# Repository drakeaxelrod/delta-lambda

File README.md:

# Delta Lambda

ZMK firmware for the Delta Lambda 34-key split keyboard, running on two Seeed XIAO nRF52840 controllers. Based on the [delta-omega](https://github.com/unspecworks/delta-omega) design.

## Layout

**Gallium** alpha layout with home row mods (GACS order), 34 combos, mouse keys, and 6 layers.

### Base (Gallium)

- **Home row mods** (GACS): Gui/Alt/Ctrl/Shift on left, mirrored on right
- **Hyper** (all 4 mods) on W and F
- **Thumb layer-taps**: ESC/Util, Space/Nav, Enter/Num, Bksp/Fun

### Nav (hold Space)

### Num (hold Enter)

### Fun (hold Backspace)

### Util + Mouse (hold Escape)

### Game (toggle from Fun layer)

## Combos

| Type | Timeout | Prior idle | Examples |
|------|---------|------------|----------|
| Vertical (top+home) | 80ms | 150ms | `@` `#` `$` `%` `^` `+` `*` `&` |
| Vertical (home+bottom) | 80ms | 150ms | `` ` `` `\` `=` `~` `_` `-` `/` `\|` |
| Horizontal (adjacent) | 40ms | 280ms | `[` `]` `<` `(` `)` `>` `{` `}` |
| Multi-key | 50ms | 200ms | Tab (3-key), CapsWord, Studio unlock |
| Thumb | — | — | LShift, RShift |

## Home Row Mods

| Setting | Value |
|---|---|
| Flavor | balanced (positional hold-tap) |
| Tapping term | 280ms |
| Quick tap | 175ms |
| Require prior idle | 150ms |
| Hold trigger | opposite hand + thumbs only |

Thumb layer-taps use **balanced** flavor with 200ms tapping term for fast layer activation.

## Hardware

| Component | Detail |
|---|---|
| Base design | [delta-omega](https://github.com/unspecworks/delta-omega) |
| Controllers | 2x Seeed XIAO nRF52840 |
| Keys | 34 (3x5 + 2 thumb per hand) |
| Switches | Kailh Choc v1 / v2 (Hotswap) |
| Matrix | 4x10 (col2row) |
| Connection | USB-C or Bluetooth (5 profiles) |

## Building

### Local (Nix)

```bash
nix develop          # enter dev shell
just init            # initialize west workspace (first time)
just build           # build left + right + settings_reset
just bootloader      # download XIAO bootloader
just update          # west update
```

Outputs go to `build/`:
- `delta-lambda-left.uf2` (central)
- `delta-lambda-right.uf2` (peripheral)
- `delta-lambda-reset.uf2` (bond/settings reset)

### GitHub Actions

Push to `config/` or `boards/` triggers a build via ZMK's reusable workflow. Download UF2 artifacts from the Actions tab.

### Regenerate layer SVGs

```bash
just gen-svg    # regenerates assets/svg/layers/*.svg from keymap
```

## Flashing

1. Double-tap reset on the XIAO to enter UF2 bootloader (mounts as `XIAO-SENSE`)
2. Copy the appropriate `.uf2` file to the mounted drive
3. Flash left half first, then right half

To clear Bluetooth bonds, flash `delta-lambda-reset.uf2` on **both** halves, then reflash the regular firmware.

## ZMK Studio

Runtime keymap editing is enabled. Unlock with the combo at thumb key positions 30 + 33.

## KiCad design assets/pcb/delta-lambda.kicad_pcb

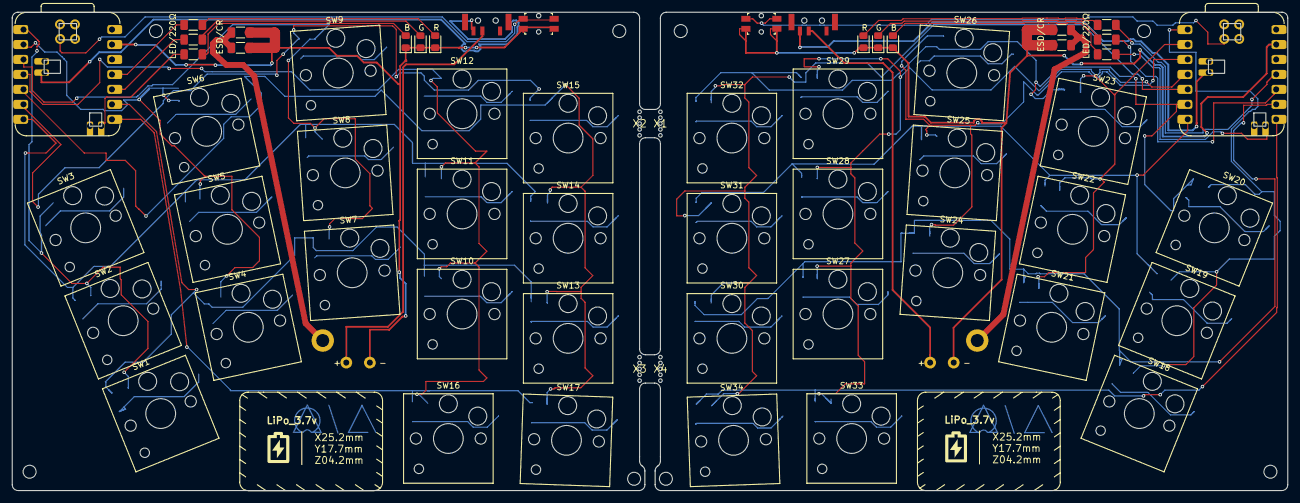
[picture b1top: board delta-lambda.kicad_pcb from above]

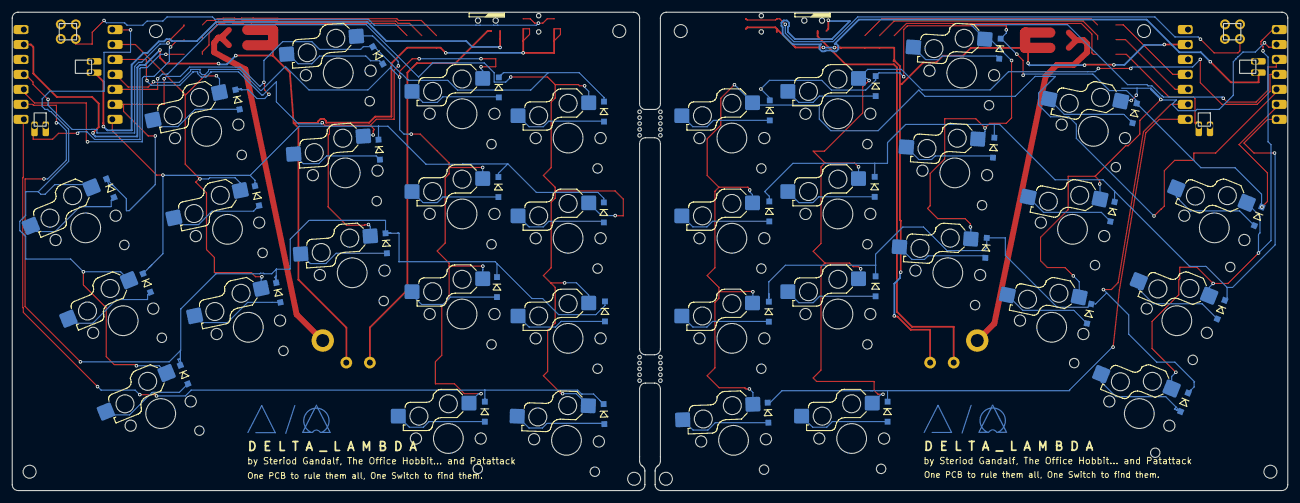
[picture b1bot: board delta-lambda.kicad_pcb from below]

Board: 2 copper layers, 216.5 x 81.2 mm, 106 parts (34 on the bottom side), 74 nets.

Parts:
C1, C2: C_1206_1NF; C_1206_3216Metric_Pad1.33x1.80mm_HandSolder
D1, D2, D3, D4, D5, D6, D7, D8, D9, D10, D11, D12, D13, D14, D15, D16, D17, D18, D19, D20, D21, D22, D23, D24, D25, D26, D27, D28, D29, D30, D31, D32, D33, D34: SOD123
H1, H2: mounting_hole_plated
L1, L4: LED_0805_R; LED_0805_2012Metric_Pad1.15x1.40mm_HandSolder
L2, L5: LED_0805_G; LED_0805_2012Metric_Pad1.15x1.40mm_HandSolder
L3, L6: LED_0805_B; LED_0805_2012Metric_Pad1.15x1.40mm_HandSolder
MCU1, MCU2: XIAO-nRF52840-SMD; smdXIAO-nRF52840
MH1, MH2, MH3, MH4, MH5, MH6, MH7, MH8: mounting_hole_npth
POWER1: PWR_SW; power_switch
PWR_SW: POWER1; power_switch
R1, R2, R3, R4, R5, R6: R_1206 _220R; R_1206_3216Metric_Pad1.30x1.75mm_HandSolder
R7, R8: R_1206_1MR; C_1206_3216Metric_Pad1.33x1.80mm_HandSolder
RST1, RST2: SW_RST; reset_switch_smd_side
SW1, SW2, SW3, SW4, SW5, SW6, SW7, SW8, SW9, SW10, SW11, SW12, SW13, SW14, SW15, SW16, SW17, SW18, SW19, SW20, SW21, SW22, SW23, SW24, SW25, SW26, SW27, SW28, SW29, SW30, SW31, SW32, SW33, SW34: ULP_SW; Hotswap_Choc_V1V2
TH1, TH2: simple_tht_fp
X1, X2, X3, X4: Mousebite_5

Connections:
L_BATP: MCU2.15, POWER1.3
L_C1: MCU2.1, SW1.1, SW2.1, SW3.1
L_C2: MCU2.2, SW4.1, SW5.1, SW6.1
L_C3: MCU2.3, SW7.1, SW8.1, SW9.1
L_C4: MCU2.4, SW10.1, SW11.1, SW12.1, SW16.1
L_C5: MCU2.5, SW13.1, SW14.1, SW15.1, SW17.1
L_CGND: C2.1, R8.1
L_GND: C2.2, L4.1, L5.1, L6.1, MCU2.13, R8.2, RST1.2, RST1.4, TH1.1
L_LED1: L4.2, R1.2
L_LED2: L5.2, R2.2
L_LED3: L6.2, R3.2
L_LED_R1: MCU2.11, R1.1
L_LED_R2: MCU2.10, R2.1
L_LED_R3: MCU2.17, R3.1
L_R1: D3.4, D6.4, D9.4, D12.4, D15.4, MCU2.6
L_R2: D2.4, D5.4, D8.4, D11.4, D14.4, MCU2.7
L_R3: D1.4, D4.4, D7.4, D10.4, D13.4, MCU2.9
L_R4: D16.4, D17.4, MCU2.8
L_RAW: POWER1.2, TH1.2
L_RST: MCU2.21, RST1.1, RST1.3
R_BATP: MCU1.15, PWR_SW.3
R_C1: MCU1.1, SW18.1, SW19.1, SW20.1
R_C2: MCU1.2, SW21.1, SW22.1, SW23.1
R_C3: MCU1.3, SW24.1, SW25.1, SW26.1
R_C4: MCU1.4, SW27.1, SW28.1, SW29.1, SW33.1
R_C5: MCU1.5, SW30.1, SW31.1, SW32.1, SW34.1
R_CGND: C1.2, R7.2
R_GND: C1.1, L1.1, L2.1, L3.1, MCU1.13, R7.1, RST2.2, RST2.4, TH2.1
R_LED1: L1.2, R4.1
R_LED2: L2.2, R5.1
R_LED3: L3.2, R6.1
R_LED_R1: MCU1.11, R4.2
R_LED_R2: MCU1.10, R5.2
R_LED_R3: MCU1.17, R6.2
R_R1: D20.4, D23.4, D26.4, D29.4, D32.4, MCU1.6
R_R2: D19.4, D22.4, D25.4, D28.4, D31.4, MCU1.7
R_R3: D18.4, D21.4, D24.4, D27.4, D30.4, MCU1.9
R_R4: D33.4, D34.4, MCU1.8
R_RAW: PWR_SW.2, TH2.2
R_RST: MCU1.21, RST2.1, RST2.3
SW1_1: D1.5, SW1.2
SW2_1: D2.5, SW2.2
SW3_1: D3.5, SW3.2
SW4_1: D4.5, SW4.2
SW5_1: D5.5, SW5.2
SW6_1: D6.5, SW6.2
SW7_1: D7.5, SW7.2
SW8_1: D8.5, SW8.2
SW9_1: D9.5, SW9.2
SW10_1: D10.5, SW10.2
SW11_1: D11.5, SW11.2
SW12_1: D12.5, SW12.2
SW13_1: D13.5, SW13.2
SW14_1: D14.5, SW14.2
SW15_1: D15.5, SW15.2
SW16_1: D16.5, SW16.2
SW17_1: D17.5, SW17.2
SW18_1: D18.5, SW18.2
SW19_1: D19.5, SW19.2
SW20_1: D20.5, SW20.2
SW21_1: D21.5, SW21.2
SW22_1: D22.5, SW22.2
SW23_1: D23.5, SW23.2
SW24_1: D24.5, SW24.2
SW25_1: D25.5, SW25.2
SW26_1: D26.5, SW26.2
SW27_1: D27.5, SW27.2
SW28_1: D28.5, SW28.2
SW29_1: D29.5, SW29.2
SW30_1: D30.5, SW30.2
SW31_1: D31.5, SW31.2
SW32_1: D32.5, SW32.2
SW33_1: D33.5, SW33.2
SW34_1: D34.5, SW34.2

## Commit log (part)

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2026-03-20 Initial plan
